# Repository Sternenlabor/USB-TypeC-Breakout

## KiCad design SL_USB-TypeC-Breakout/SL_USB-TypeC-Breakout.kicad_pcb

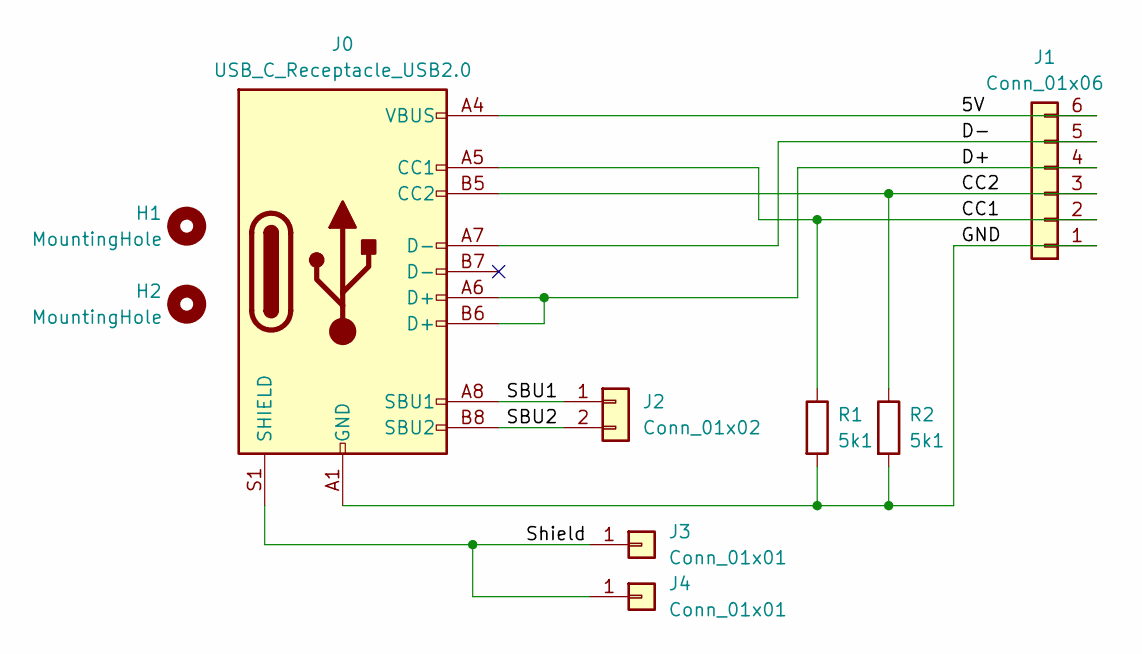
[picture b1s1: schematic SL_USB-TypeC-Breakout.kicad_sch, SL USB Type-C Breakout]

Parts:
H1, H2: MountingHole; MountingHole_3.2mm_M3
J0: USB_C_Receptacle_USB2.0; USB_C_Receptacle_GCT_USB4105-xx-A_16P_TopMnt_Horizontal
J1: Conn_01x06; PinHeader_1x06_P2.54mm_Vertical
J2: Conn_01x02; PinHeader_1x02_P2.54mm_Vertical
J3, J4: Conn_01x01; Pin_D1.0mm_L10.0mm
R1, R2: 5k1; R_0603_1608Metric_Pad0.98x0.95mm_HandSolder

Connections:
/5V: J0.A4 (VBUS), J0.A9 (VBUS), J0.B4 (VBUS), J0.B9 (VBUS), J1.6
/CC1: J0.A5 (CC1), J1.2, R1.1
/CC2: J0.B5 (CC2), J1.3, R2.1
/D+: J0.A6 (D+), J0.B6 (D+), J1.4
/D-: J0.A7 (D-), J1.5
/GND: J0.A1 (GND), J0.A12 (GND), J0.B1 (GND), J0.B12 (GND), J1.1, R1.2, R2.2
/SBU1: J0.A8 (SBU1), J2.1
/SBU2: J0.B8 (SBU2), J2.2
/Shield: J0.S1 (SHIELD), J3.1, J4.1

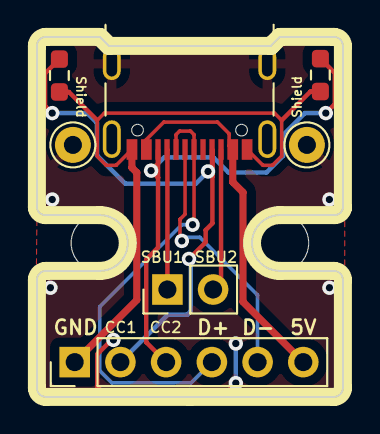
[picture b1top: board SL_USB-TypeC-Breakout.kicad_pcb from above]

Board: 2 copper layers, 17.0 x 20.0 mm, 9 parts (0 on the bottom side), 9 nets.

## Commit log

2024-02-23 ༼ つ ◕_◕ ༽つ initial commit
